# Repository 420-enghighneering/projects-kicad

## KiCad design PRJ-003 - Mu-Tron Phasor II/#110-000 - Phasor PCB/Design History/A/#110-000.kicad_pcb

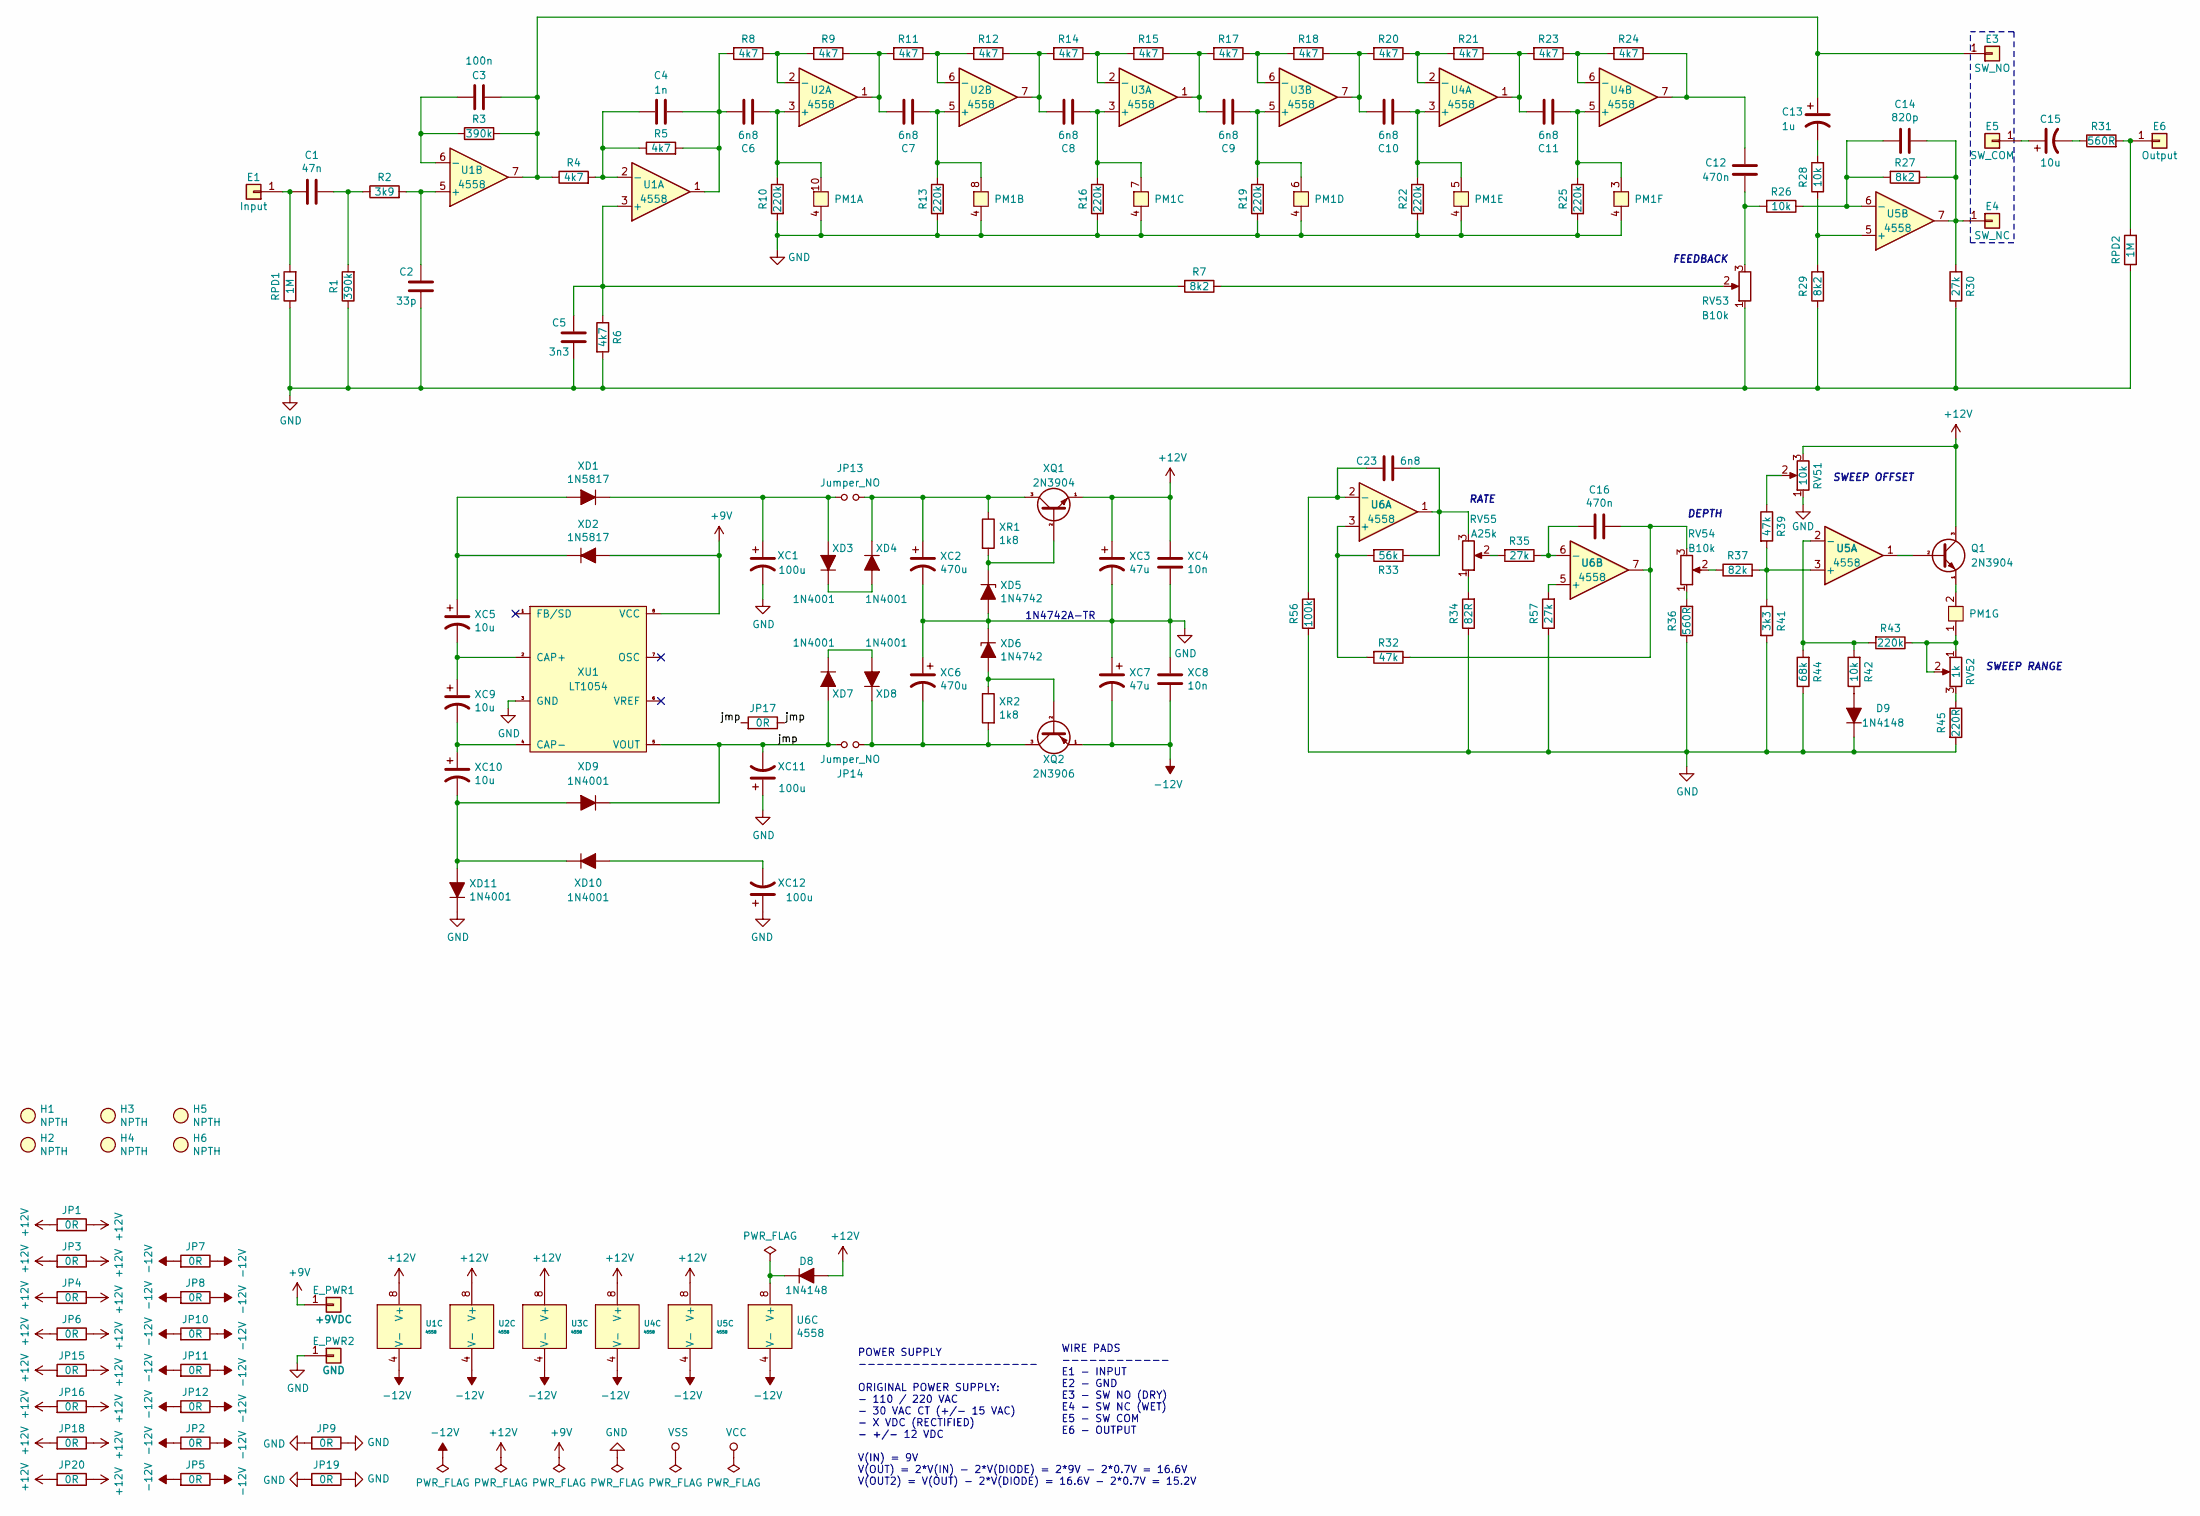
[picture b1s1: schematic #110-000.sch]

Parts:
C1: 47n; C_MKS2F024701C00KSSD
C2: 33p; C_FKP2O100331D00JSSD
C3: 100n; C_MKS2C031001A00KSSD
C4: 1n; C_FKS2G011001A00KSSD
C5: 3n3; C_FKS2G013301A00KSSD
C6, C7, C8, C9, C10, C11, C23: 6n8; C_FKS2G016801B00KSSD
C12, C16: 470n; C_MKS2C034701C00KSSD
C13: 1u; C_UMA1H010MDD
C14: 820p; C_FKP2J008201D00HSSD
C15: 10u; C_UMA1V100MDD
D8, D9: 1N4148; D_P10.16
E1: Input; E_WIRE_PAD
E3: SW_NO; E_WIRE_PAD
E4: SW_NC; E_WIRE_PAD
E5: SW_COM; E_WIRE_PAD
E6: Output; E_WIRE_PAD
E_PWR1: +9VDC; E_WIRE_PAD
E_PWR2: GND; E_WIRE_PAD
H1, H2, H3, H4, H5, H6: NPTH; E_ZIPTIE_NPTH
JP1, JP2, JP3, JP4, JP5, JP6, JP7, JP8, JP9, JP10, JP11, JP12, JP15, JP16, JP17, JP18, JP19, JP20: 0R; R_0R_JUMPER_P10.16
JP13, JP14: Jumper_NO; R_NO_JUMPER_P10.16
PM1: Photomodule; PM_DIP-10
Q1: 2N3904; Q_P2.54
R1, R3: 390k; R_P10.16
R2: 3k9; R_P10.16
R4, R5, R6, R8, R9, R11, R12, R14, R15, R17, R18, R20, R21, R23, R24: 4k7; R_P10.16
R7, R27, R29: 8k2; R_P10.16
R10, R13, R16, R19, R22, R25, R43: 220k; R_P10.16
R26, R28, R42: 10k; R_P10.16
R30, R35, R57: 27k; R_P10.16
R31, R36: 560R; R_P10.16
R32, R39: 47k; R_P10.16
R33: 56k; R_P10.16
R34: 82R; R_P10.16
R37: 82k; R_P10.16
R41: 3k3; R_P10.16
R44: 68k; R_P10.16
R45: 220R; R_P10.16
R56: 100k; R_P10.16
RPD1, RPD2: 1M; R_P10.16
RV51: 10k; R_TRIM
RV52: 1k; R_TRIM
RV53, RV54: B10k; R_POT
RV55: A25k; R_POT
U1, U2, U3, U4, U5, U6: 4558; U_DIP-8
XC1, XC11, XC12: 100u; C_UMA1E101MDD
XC2, XC6: 470u; C_ANGLED
XC3, XC7: 47u; C_UMA1V470MDD
XC4, XC8: 10n; C_FKS2G021001C00KSSD
XC5, XC9, XC10: 10u; C_UMA1V100MDD
XD1, XD2: 1N5817; D_P10.16
XD3, XD4, XD7, XD8, XD9, XD10, XD11: 1N4001; D_P10.16
XD5, XD6: 1N4742; D_P10.16
XQ1: 2N3904; Q_P2.54
XQ2: 2N3906; Q_P2.54
XR1, XR2: 1k8; R_P10.16
XU1: LT1054; U_DIP-8

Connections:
+9V: E_PWR1.1, XD2.1 (A), XU1.8 (VCC)
+12V: D8.1 (A), JP1.1, JP1.2, JP3.1, JP3.2, JP4.1, JP4.2, JP6.1, JP6.2, JP15.1, JP15.2, JP16.1, JP16.2, JP18.1, JP18.2, JP20.1, JP20.2, Q1.3 (C), RV51.3, U1.8 (V+), U2.8 (V+), U3.8 (V+), U4.8 (V+), U5.8 (V+), XC3.1, XC4.1, XQ1.1 (E)
-12V: JP2.1, JP2.2, JP5.1, JP5.2, JP7.1, JP7.2, JP8.1, JP8.2, JP10.1, JP10.2, JP11.1, JP11.2, JP12.1, JP12.2, U1.4 (V-), U2.4 (V-), U3.4 (V-), U4.4 (V-), U5.4 (V-), U6.4 (V-), XC7.2, XC8.2, XQ2.1 (E)
/jmp: JP14.1, JP17.1, JP17.2, XC11.2, XD7.1 (A), XD9.2 (K), XU1.5 (VOUT)
GND: C2.2, C5.2, D9.2 (K), E_PWR2.1, JP9.1, JP9.2, JP19.1, JP19.2, PM1.4, PM1.9, R1.1, R6.2, R10.2, R13.2, R16.2, R19.2, R22.2, R25.2, R29.1, R30.1, R34.1, R36.1, R41.2, R44.1, R45.2, R56.1, R57.1, RPD1.1, RPD2.1, RV51.1, RV53.1, XC1.2, XC2.2, XC3.2, XC4.2, XC6.1, XC7.1, XC8.1, XC11.1, XC12.1, XD5.1 (A), XD6.2 (K), XD11.2 (K), XU1.3 (GND)
unnamed: C1.1, E1.1, RPD1.2
unnamed: C1.2, R1.2, R2.1
unnamed: C2.1, R2.2, U1.5 (+)
unnamed: C3.1, R3.1, U1.6 (-)
unnamed: C4.1, R4.2, R5.1, U1.2 (-)
unnamed: C4.2, C6.1, R5.2, R8.2, U1.1
unnamed: C5.1, R6.1, R7.2, U1.3 (+)
unnamed: C6.2, PM1.10, R10.1, U2.3 (+)
unnamed: C7.1, R9.1, R11.2, U2.1
unnamed: C7.2, PM1.8, R13.1, U2.5 (+)
unnamed: C8.1, R12.1, R14.2, U2.7
unnamed: C8.2, PM1.7, R16.1, U3.3 (+)
unnamed: C9.1, R15.1, R17.2, U3.1
unnamed: C9.2, PM1.6, R19.1, U3.5 (+)
unnamed: C10.1, R18.1, R20.2, U3.7
unnamed: C10.2, PM1.5, R22.1, U4.3 (+)
unnamed: C11.1, R21.1, R23.2, U4.1
unnamed: C11.2, PM1.3, R25.1, U4.5 (+)
unnamed: C12.1, R24.1, U4.7
unnamed: C12.2, R26.2, RV53.3
unnamed: C3.2, C13.1, E3.1, R3.2, R4.1, U1.7
unnamed: C13.2, R28.2
unnamed: C14.1, R26.1, R27.2, U5.6 (-)
unnamed: C14.2, E4.1, R27.1, R30.2, U5.7
unnamed: C15.1, E5.1
unnamed: C15.2, R31.1
unnamed: C16.1, R35.1, U6.6 (-)
unnamed: C16.2, R32.1, RV54.3, U6.7
unnamed: C23.1, R56.2, U6.2 (-)
unnamed: C23.2, R33.1, RV55.3, U6.1
unnamed: D8.2 (K), U6.8 (V+)
unnamed: D9.1 (A), R42.1
unnamed: E6.1, R31.2, RPD2.2
unnamed: JP13.1, XC1.1, XD1.2 (K), XD3.1 (A)
unnamed: JP13.2, XC2.1, XD4.2 (K), XQ1.3 (C), XR1.1
unnamed: JP14.2, XC6.2, XD8.2 (K), XQ2.3 (C), XR2.2
unnamed: PM1.1, R43.1, RV52.1, RV52.2
unnamed: PM1.2, Q1.1 (E)
unnamed: Q1.2 (B), U5.1
unnamed: R7.1, RV53.2
unnamed: R8.1, R9.2, U2.2 (-)
unnamed: R11.1, R12.2, U2.6 (-)
unnamed: R14.1, R15.2, U3.2 (-)
unnamed: R17.1, R18.2, U3.6 (-)
unnamed: R20.1, R21.2, U4.2 (-)
unnamed: R23.1, R24.2, U4.6 (-)
unnamed: R28.1, R29.2, U5.5 (+)
unnamed: R32.2, R33.2, U6.3 (+)
unnamed: R34.2, RV55.1
unnamed: R35.2, RV55.2
unnamed: R36.2, RV54.1
unnamed: R37.1, RV54.2
unnamed: R37.2, R39.2, R41.1, U5.3 (+)
unnamed: R39.1, RV51.2
unnamed: R42.2, R43.2, R44.2, U5.2 (-)
unnamed: R45.1, RV52.3
unnamed: R57.2, U6.5 (+)
unnamed: XC5.1, XD1.1 (A), XD2.2 (K)
unnamed: XC5.2, XC9.1, XU1.2 (CAP+)
unnamed: XC9.2, XC10.1, XU1.4 (CAP-)
unnamed: XC10.2, XD9.1 (A), XD10.2 (K), XD11.1 (A)
unnamed: XC12.2, XD10.1 (A)
unnamed: XD3.2 (K), XD4.1 (A)
unnamed: XD5.2 (K), XQ1.2 (B), XR1.2
unnamed: XD6.1 (A), XQ2.2 (B), XR2.1
unnamed: XD7.2 (K), XD8.1 (A)

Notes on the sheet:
1N4742A-TR
POWER SUPPLY -------------------- ORIGINAL POWER SUPPLY: - 110 / 220 VAC - 30 VAC CT (+/- 15 VAC) - X VDC (RECTIFIED) - +/- 12 VDC V(IN) = 9V V(OUT) = 2*V(IN) - 2*V(DIODE) = 2*9V - 2*0.7V = 16.6V V(OUT2) = V(OUT) - 2*V(DIODE) = 16.6V - 2*0.7V = 15.2V
SWEEP OFFSET
SWEEP RANGE
DEPTH
RATE
FEEDBACK
WIRE PADS ------------ E1 - INPUT E2 - GND E3 - SW NO (DRY) E4 - SW NC (WET) E5 - SW COM E6 - OUTPUT

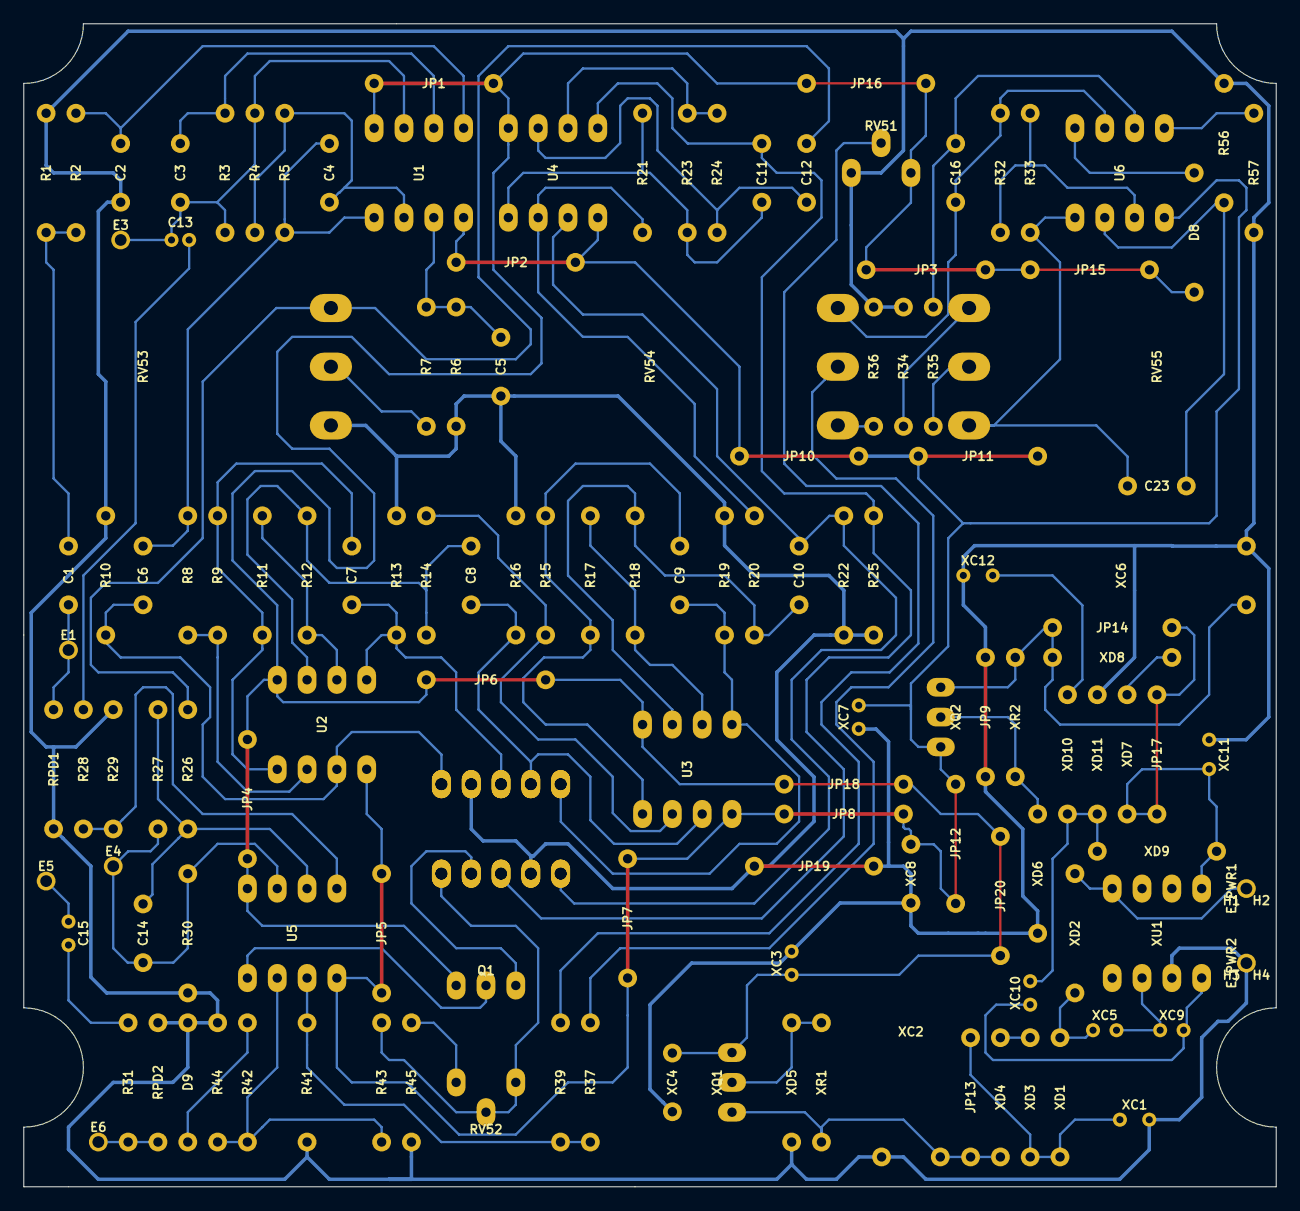
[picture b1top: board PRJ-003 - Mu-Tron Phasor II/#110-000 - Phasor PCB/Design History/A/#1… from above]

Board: 2 copper layers, 106.7 x 99.1 mm, 140 parts (0 on the bottom side), 71 nets.

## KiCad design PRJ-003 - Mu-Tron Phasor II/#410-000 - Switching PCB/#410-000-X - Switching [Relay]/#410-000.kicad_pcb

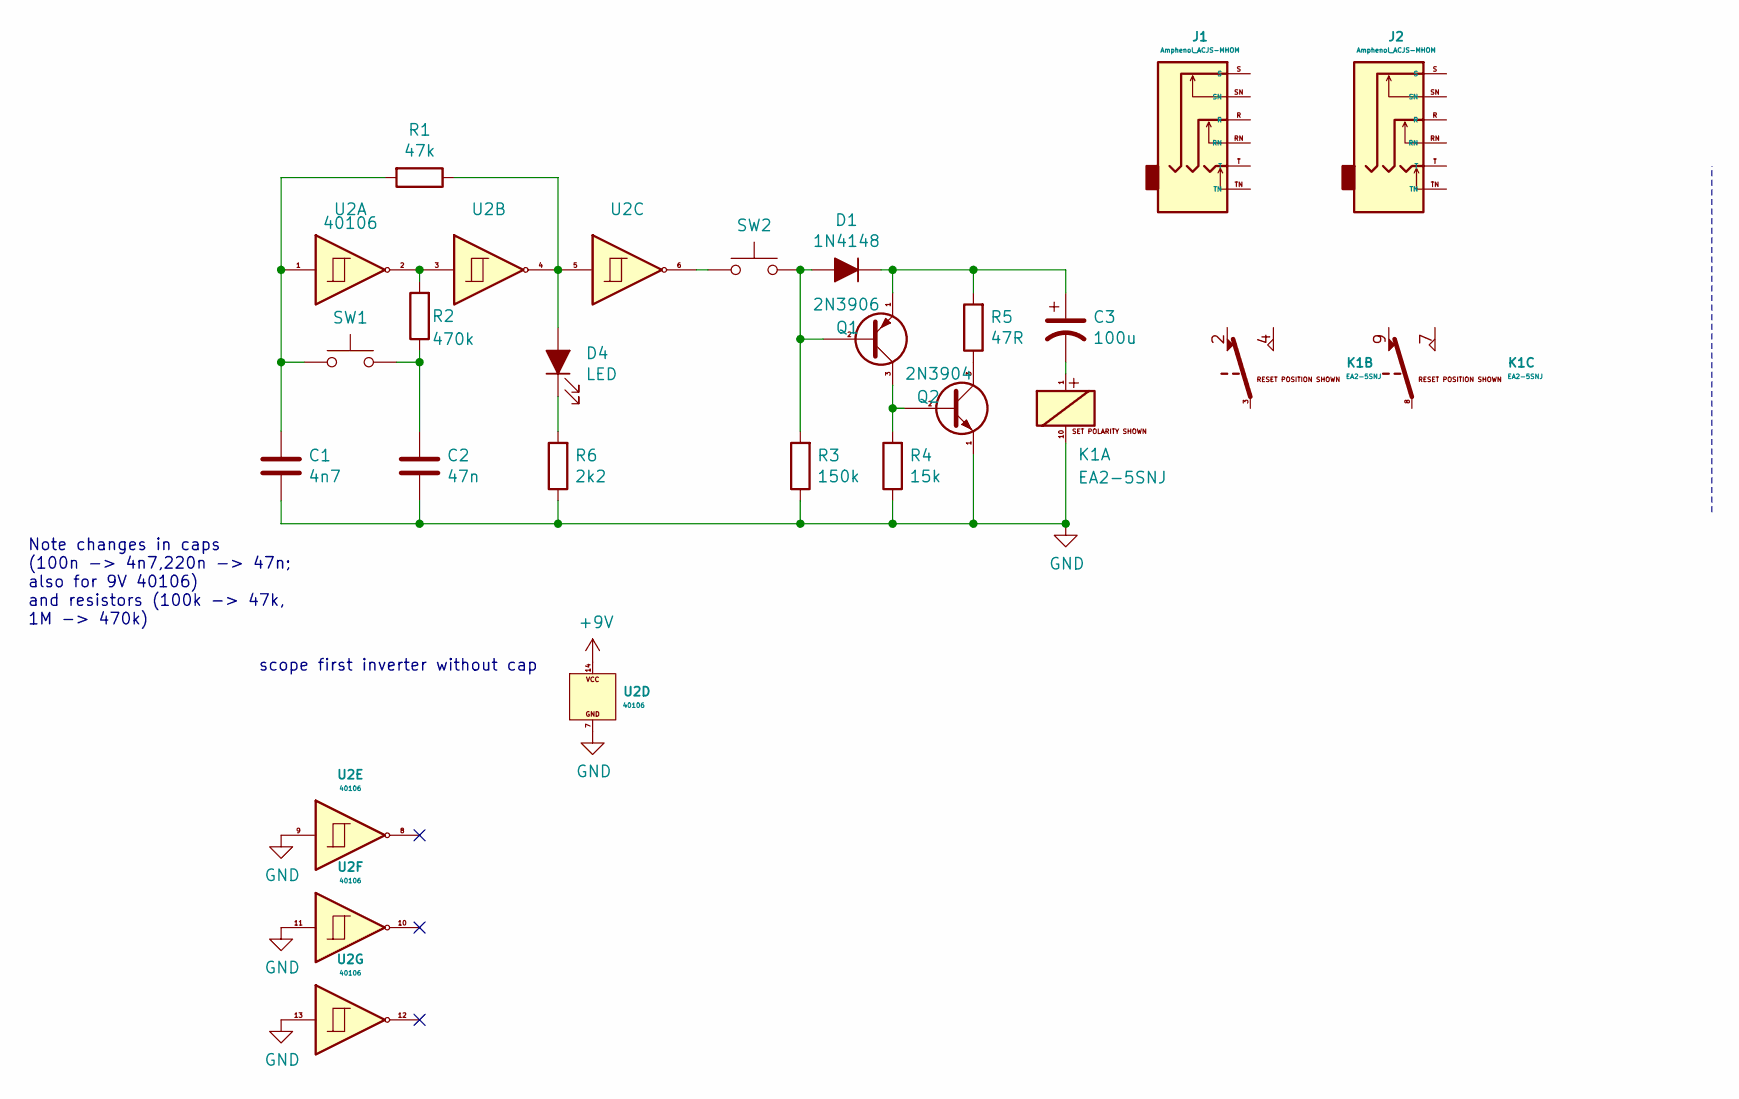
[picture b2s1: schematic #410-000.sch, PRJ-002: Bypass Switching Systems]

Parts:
C1: 4n7; C_FKS2G014701A00KSSD
C2: 47n; C_MKS2F024701C00KSSD
C3: 100u; C_UMA1V100MDD
D1: 1N4148; D_P10.16_DO35
D4: LED; E_WIRE_PAD_2x
J1, J2: Amphenol_ACJS-MHOM; J_AC
K1: EA2-5SNJ; U_DIP-10
Q1: 2N3906; Q_P2.54
Q2: 2N3904; Q_P2.54
R1: 47k; R_P10.16
R2: 470k; R_P10.16
R3: 150k; R_P10.16
R4: 15k; R_P10.16
R5: 47R; R_P10.16
R6: 2k2; R_P10.16
SW1, SW2: SW_Push; E_WIRE_PAD_2x
U2: 40106; Texas_Instruments_CD40106BE

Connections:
+9V: U2.14
GND: C1.2, C2.2, K1.10, Q2.1 (E), R3.1, R4.1, R6.1, U2.7, U2.9, U2.11, U2.13
unnamed: C1.1, R1.2, SW1.1, U2.1
unnamed: C2.1, R2.1, SW1.2
unnamed: C3.1, D1.2 (K), Q1.1 (E), R5.2
unnamed: C3.2, K1.1
unnamed: D1.1 (A), Q1.2 (B), R3.2, SW2.2
unnamed: D4.1 (K), R6.2
unnamed: D4.2 (A), R1.1, U2.4, U2.5
unnamed: Q1.3 (C), Q2.2 (B), R4.2
unnamed: Q2.3 (C), R5.1
unnamed: R2.2, U2.2, U2.3
unnamed: SW2.1, U2.6

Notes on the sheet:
scope first inverter without cap
Note changes in caps (100n -> 4n7,220n -> 47n; also for 9V 40106) and resistors (100k -> 47k, 1M -> 470k)

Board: 2 copper layers, 19 parts (0 on the bottom side), 12 nets, no tracks yet.

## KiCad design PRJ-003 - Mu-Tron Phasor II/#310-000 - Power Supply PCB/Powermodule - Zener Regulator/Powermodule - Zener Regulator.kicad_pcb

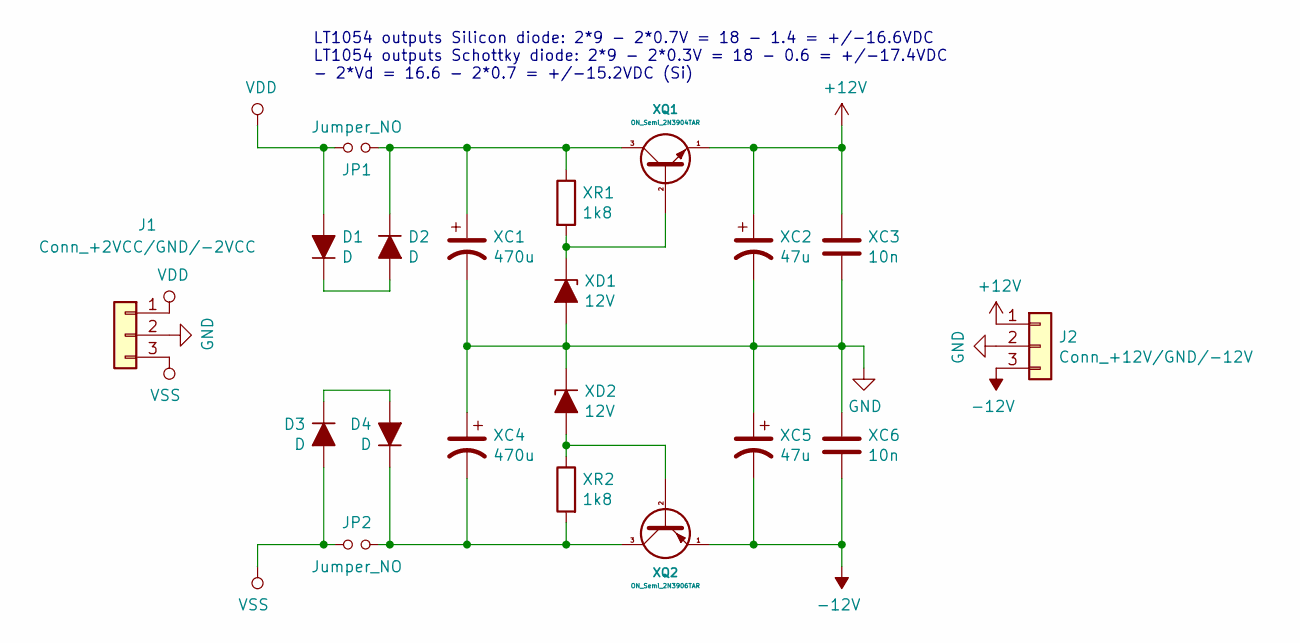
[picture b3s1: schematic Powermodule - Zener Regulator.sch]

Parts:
D1, D2, D3, D4: D; DO-41_P2.54
J1: Conn_+2VCC/GND/-2VCC; PinHeader_1x03_P2.54mm_Vertical_Top
J2: Conn_+12V/GND/-12V; PinHeader_1x03_P2.54mm_Vertical_Top
JP1, JP2: Jumper_NO; R_0R_Wire_Jumper_P2.54
XC1, XC4: 470u; Electrolytic_Radial_Angled_D10.0_H17.0_P5.0
XC2, XC5: 47u; 47uF_35V_8x5x2.5_UMA1V470MDD
XC3, XC6: 10n; Wima_FKS2G021001C00KSSD
XD1, XD2: 12V; DO-41_P2.54
XQ1: ON_Semi_2N3904TAR
XQ2: ON_Semi_2N3906TAR
XR1, XR2: 1k8; R_CC25_P2.54_V

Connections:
+12V: J2.1, XC2.1, XC3.1, XQ1.1 (E)
-12V: J2.3, XC5.2, XC6.2, XQ2.1 (E)
GND: J1.2, J2.2, XC1.2, XC2.2, XC3.2, XC4.1, XC5.1, XC6.1, XD1.1 (A), XD2.2 (K)
unnamed: D1.2 (K), D2.1 (A)
unnamed: D2.2 (K), JP1.2, XC1.1, XQ1.3 (C), XR1.1
unnamed: D3.2 (K), D4.1 (A)
unnamed: D4.2 (K), JP2.2, XC4.2, XQ2.3 (C), XR2.2
unnamed: XD1.2 (K), XQ1.2 (B), XR1.2
unnamed: XD2.1 (A), XQ2.2 (B), XR2.1
VDD: D1.1 (A), J1.1, JP1.1
VSS: D3.1 (A), J1.3, JP2.1

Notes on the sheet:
LT1054 outputs Silicon diode: 2*9 - 2*0.7V = 18 - 1.4 = +/-16.6VDC LT1054 outputs Schottky diode: 2*9 - 2*0.3V = 18 - 0.6 = +/-17.4VDC - 2*Vd = 16.6 - 2*0.7 = +/-15.2VDC (Si)

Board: 2 copper layers, 20 parts (0 on the bottom side), 11 nets, no tracks yet.

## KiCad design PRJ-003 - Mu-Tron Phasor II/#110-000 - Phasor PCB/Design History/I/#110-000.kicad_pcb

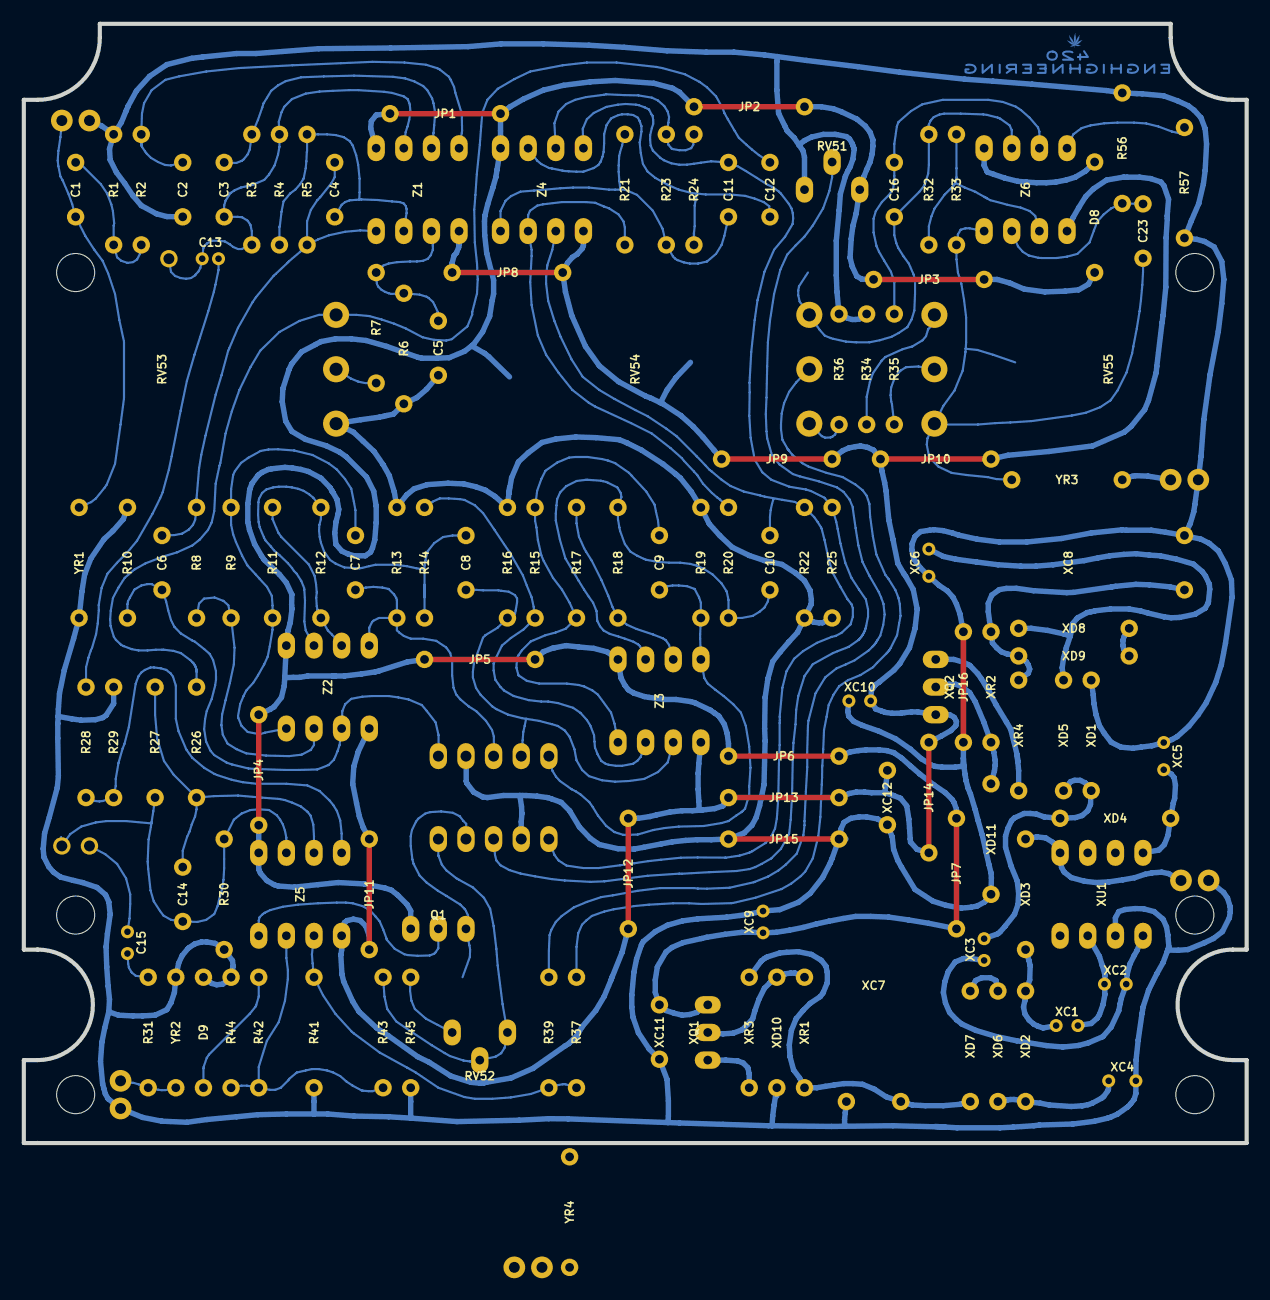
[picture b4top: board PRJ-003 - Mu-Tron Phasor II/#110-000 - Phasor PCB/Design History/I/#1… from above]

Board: 2 copper layers, 112.4 x 102.9 mm, 152 parts (0 on the bottom side), 75 nets.

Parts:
C1: 47n; C_MKS2F024701C00KSSD
C2: 33p; C_FKP2O100331D00JSSD
C3: 100n; C_MKS2C031001A00KSSD
C4: 1n; C_FKS2G011001A00KSSD
C5: 3n3; C_FKS2G013301A00KSSD
C6, C7, C8, C9, C10, C11, C23: 6n8; C_FKS2G016801B00KSSD
C12, C16: 470n; C_MKS2C034701C00KSSD
C13: 1u; C_UMA1H010MDD
C14: 820p; C_FKP2J008201D00HSSD
C15: 10u; C_UMA1V100MDD
D8, D9: 1N4148; D_P10.16_DO35
E0: Power Supply; E_WIRE_PAD_2x
E1: Input & Shield; E_WIRE_PAD_2x
E3: SW_NO; E_WIRE_PAD
E4: SW_NC; E_WIRE_PAD
E5: SW_COM; E_WIRE_PAD
E6: Output & Shield; E_WIRE_PAD_2x
H_A1, H_A2, H_A3, H_A4, H_A5, H_A6: NPTH; H_NPTH
H_B1, H_B2, H_B3, H_B4, H_B5, H_B6: NPTH; E_ZIPTIE_NPTH
JP1, JP2, JP3, JP4, JP5, JP6, JP7, JP8, JP9, JP10, JP11, JP12, JP13, JP14, JP15, JP16: 0R; R_0R_JUMPER_P10.16
PM1: Photomodule; PM_DIP-10
Q1: 2N3904; Q_P2.54
R1, R3: 390k; R_P10.16
R2: 3k9; R_P10.16
R4, R5, R6, R8, R9, R11, R12, R14, R15, R17, R18, R20, R21, R23, R24: 4k7; R_P10.16
R7, R27, R29: 8k2; R_P10.16
R10, R13, R16, R19, R22, R25, R43: 220k; R_P10.16
R26, R28, R42: 10k; R_P10.16
R30, R35, R57: 27k; R_P10.16
R31, R36: 560R; R_P10.16
R32, R39: 47k; R_P10.16
R33: 56k; R_P10.16
R34: 82R; R_P10.16
R37: 82k; R_P10.16
R41: 3k3; R_P10.16
R44: 68k; R_P10.16
R45: 220R; R_P10.16
R56: 100k; R_P10.16
RV51: 10k; R_TRIM
RV52: 1k; R_TRIM
RV53, RV54: B10k; R_POT
RV55: A25k; R_POT
TP1: TP1; TP_SMD_R_3mm
TP2: TP2; TP_SMD_R_3mm
TP3: TP3; TP_SMD_R_3mm
TP4: TP4; TP_SMD_R_3mm
TP5: TP5; TP_SMD_R_3mm
XC1, XC2, XC3: 10u; C_UMA1V100MDD
XC4, XC5, XC6: 100u; C_UMA1E101MDD
XC7, XC8: 470u; C_ANGLED
XC9, XC10: 47u; C_UMA1V470MDD
XC11, XC12: 10n; C_FKS2G021001C00KSSD
XD1, XD4, XD5, XD6, XD7, XD8, XD9: 1N4001; D_P10.16
XD2, XD3: 1N5817; D_P10.16
XD10, XD11: 1N4742; D_P10.16_DO35
XQ1: 2N3904; Q_P2.54
XQ2: 2N3906; Q_P2.54
XR1, XR2: 1k8; R_P10.16
XR3, XR4: 100R; R_P10.16
XU1: LT1054; U_DIP-8
YD1: LED_RATE_1; E_WIRE_PAD_2x
YD2: LED_RATE_2; E_WIRE_PAD_2x
YR1, YR2: 1M; R_P10.16
YR3, YR4: CLR; R_P10.16
Z1, Z2, Z3, Z4, Z5, Z6: 4558; U_DIP-8

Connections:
+9V: E0.1, XD3.1, XU1.8
+12V: D8.1, JP1.1, JP1.2, JP2.1, JP2.2, JP3.1, JP3.2, JP4.1, JP4.2, JP5.1, JP5.2, JP6.1, JP6.2, JP7.1, JP7.2, Q1.3, RV51.3, TP1.1, XC9.1, XC11.1, XQ1.1, Z1.8, Z2.8, Z3.8, Z4.8, Z5.8
-12V: JP8.1, JP8.2, JP9.1, JP9.2, JP10.1, JP10.2, JP11.1, JP11.2, JP12.1, JP12.2, JP13.1, JP13.2, JP14.1, JP14.2, TP2.1, XC10.2, XC12.2, XQ2.1, Z1.4, Z2.4, Z3.4, Z4.4, Z5.4, Z6.4
GND: C2.2, C5.2, D9.2, E0.2, E1.2, E6.2, JP15.1, JP15.2, JP16.1, JP16.2, PM1.4, PM1.9, R1.1, R6.2, R10.2, R13.2, R16.2, R19.2, R22.2, R25.2, R29.1, R30.1, R34.1, R36.1, R41.2, R44.1, R45.2, R56.1, R57.1, RV51.1, RV53.1, XC4.2, XC5.1, XC6.1, XC7.2, XC8.1, XC9.2, XC10.1, XC11.2, XC12.1, XD1.2, XD10.1, XD11.2, XU1.3, YD1.1, YD2.1, YR1.1, YR2.1
unnamed: C1.1, E1.1, YR1.2
unnamed: C1.2, R1.2, R2.1
unnamed: C2.1, R2.2, Z1.5
unnamed: C3.1, R3.1, Z1.6
unnamed: C4.1, R4.2, R5.1, Z1.2
unnamed: C4.2, C6.1, R5.2, R8.2, Z1.1
unnamed: C5.1, R6.1, R7.2, Z1.3
unnamed: C6.2, PM1.10, R10.1, Z2.3
unnamed: C7.1, R9.1, R11.2, Z2.1
unnamed: C7.2, PM1.8, R13.1, Z2.5
unnamed: C8.1, R12.1, R14.2, Z2.7
unnamed: C8.2, PM1.7, R16.1, Z3.3
unnamed: C9.1, R15.1, R17.2, Z3.1
unnamed: C9.2, PM1.6, R19.1, Z3.5
unnamed: C10.1, R18.1, R20.2, Z3.7
unnamed: C10.2, PM1.5, R22.1, Z4.3
unnamed: C11.1, R21.1, R23.2, Z4.1
unnamed: C11.2, PM1.3, R25.1, Z4.5
unnamed: C12.1, R24.1, Z4.7
unnamed: C12.2, R26.2, RV53.3
unnamed: C3.2, C13.1, E3.1, R3.2, R4.1, Z1.7
unnamed: C13.2, R28.2
unnamed: C14.1, R26.1, R27.2, Z5.6
unnamed: C14.2, E4.1, R27.1, R30.2, Z5.7
unnamed: C15.1, E5.1
unnamed: C15.2, R31.1
unnamed: C16.1, R35.1, Z6.6
unnamed: C16.2, R32.1, RV54.3, TP5.1, Z6.7
unnamed: C23.1, R56.2, Z6.2
unnamed: C23.2, R33.1, RV55.3, TP3.1, YR3.2, Z6.1
unnamed: D8.2, Z6.8
unnamed: D9.1, R42.1
unnamed: E6.1, R31.2, YR2.2
unnamed: PM1.1, R43.1, RV52.1, RV52.2
unnamed: PM1.2, Q1.1, TP4.1, YR4.2
unnamed: Q1.2, Z5.1
unnamed: R7.1, RV53.2
unnamed: R8.1, R9.2, Z2.2
unnamed: R11.1, R12.2, Z2.6
unnamed: R14.1, R15.2, Z3.2
unnamed: R17.1, R18.2, Z3.6
unnamed: R20.1, R21.2, Z4.2
unnamed: R23.1, R24.2, Z4.6
unnamed: R28.1, R29.2, Z5.5
unnamed: R32.2, R33.2, Z6.3
unnamed: R34.2, RV55.1
unnamed: R35.2, RV55.2
unnamed: R36.2, RV54.1
unnamed: R37.1, RV54.2
unnamed: R37.2, R39.2, R41.1, Z5.3
unnamed: R39.1, RV51.2
unnamed: R42.2, R43.2, R44.2, Z5.2
unnamed: R45.1, RV52.3
unnamed: R57.2, Z6.5
unnamed: XC1.1, XD2.1, XD3.2
unnamed: XC1.2, XC2.1, XU1.2
unnamed: XC2.2, XC3.1, XU1.4
unnamed: XC3.2, XD1.1, XD4.1, XD5.2
unnamed: XC4.1, XD2.2, XD6.1
unnamed: XC5.2, XD4.2, XU1.5
unnamed: XC6.2, XD5.1, XD8.1
unnamed: XC7.1, XD7.2, XR1.1, XR3.2
unnamed: XC8.2, XD9.2, XR2.2, XR4.2
unnamed: XD6.2, XD7.1
unnamed: XD8.2, XD9.1
unnamed: XD10.2, XQ1.2, XR1.2
unnamed: XD11.1, XQ2.2, XR2.1
unnamed: XQ1.3, XR3.1
unnamed: XQ2.3, XR4.1
unnamed: YD1.2, YR3.1
unnamed: YD2.2, YR4.1

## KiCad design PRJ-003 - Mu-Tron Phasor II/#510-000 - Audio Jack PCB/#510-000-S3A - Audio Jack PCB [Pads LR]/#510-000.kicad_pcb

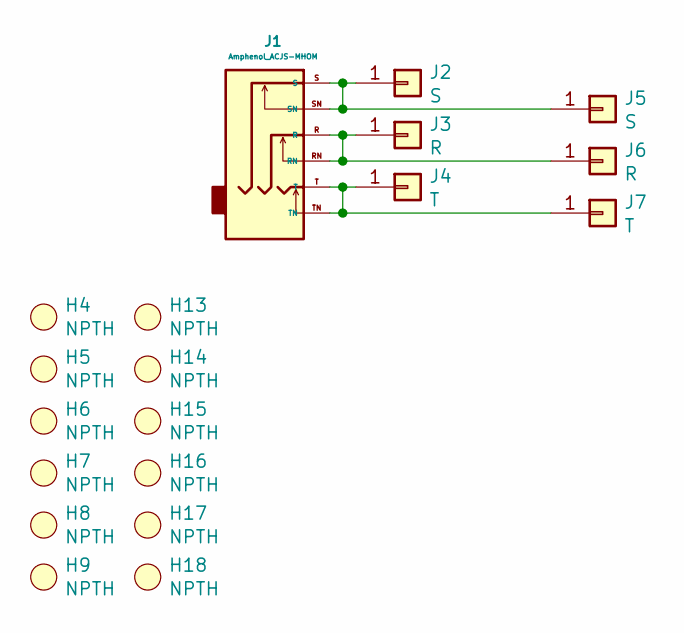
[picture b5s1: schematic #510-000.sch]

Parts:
H4, H5, H6, H7, H8, H9, H13, H14, H15, H16, H17, H18: NPTH; E_ZIPTIE_NPTH
J1: Amphenol_ACJS-MHOM; J_AC_NOCHASSIS
J2, J5: S; E_WIRE_PAD
J3, J6: R; E_WIRE_PAD
J4, J7: T; E_WIRE_PAD

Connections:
unnamed: J1.R, J1.RN, J3.1, J6.1
unnamed: J1.S, J1.SN, J2.1, J5.1
unnamed: J1.T, J1.TN, J4.1, J7.1

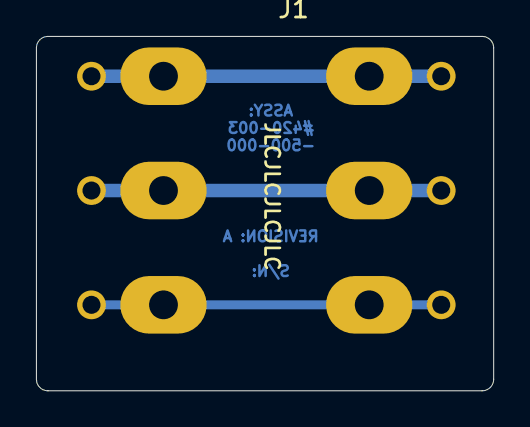
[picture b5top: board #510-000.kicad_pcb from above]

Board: 2 copper layers, 25.4 x 19.7 mm, 19 parts (0 on the bottom side), 3 nets.

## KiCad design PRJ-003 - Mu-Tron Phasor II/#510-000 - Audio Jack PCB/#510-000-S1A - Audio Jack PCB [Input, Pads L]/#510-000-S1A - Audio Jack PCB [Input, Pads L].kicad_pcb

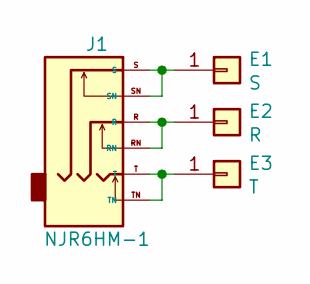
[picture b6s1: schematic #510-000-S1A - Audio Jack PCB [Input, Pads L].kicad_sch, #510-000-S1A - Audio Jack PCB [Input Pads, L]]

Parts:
E1: S; E_WIRE_PAD_1x_ZIPTIE_NPTH_2x_NARROW
E2: R; E_WIRE_PAD_1x_ZIPTIE_NPTH_2x_NARROW
E3: T; E_WIRE_PAD_1x_ZIPTIE_NPTH_2x_NARROW
J1: NJR6HM-1; J_AC_NOCHASSIS

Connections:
unnamed: E1.1, J1.S, J1.SN
unnamed: E2.1, J1.R, J1.RN
unnamed: E3.1, J1.T, J1.TN

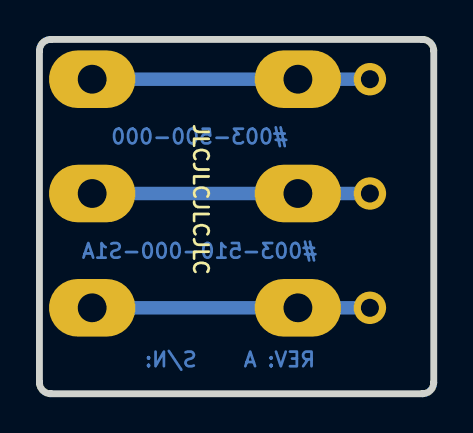
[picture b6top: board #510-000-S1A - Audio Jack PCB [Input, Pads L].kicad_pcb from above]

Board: 2 copper layers, 21.9 x 19.7 mm, 4 parts (0 on the bottom side), 3 nets.

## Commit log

2021-03-29 Initial production prototype
    Initial production prototype
